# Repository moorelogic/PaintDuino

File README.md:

# PaintDuino

## Introduction
The PaintDuino is an Arduino Leonardo compatible, universal paintball marker control board.

### Features:
* Easily programmed with Arduino IDE
* Interface for 128 x 32 OLED display
* Two high current solenoid drivers
* RGB LED for status and trigger programming
* Supports both switched and push button On/Off
* USB Mini B programming connector
* Near zero battery drain when powered off

## License
This work is licensed under a Creative Commons Attribution-ShareAlike 3.0 Unported License.

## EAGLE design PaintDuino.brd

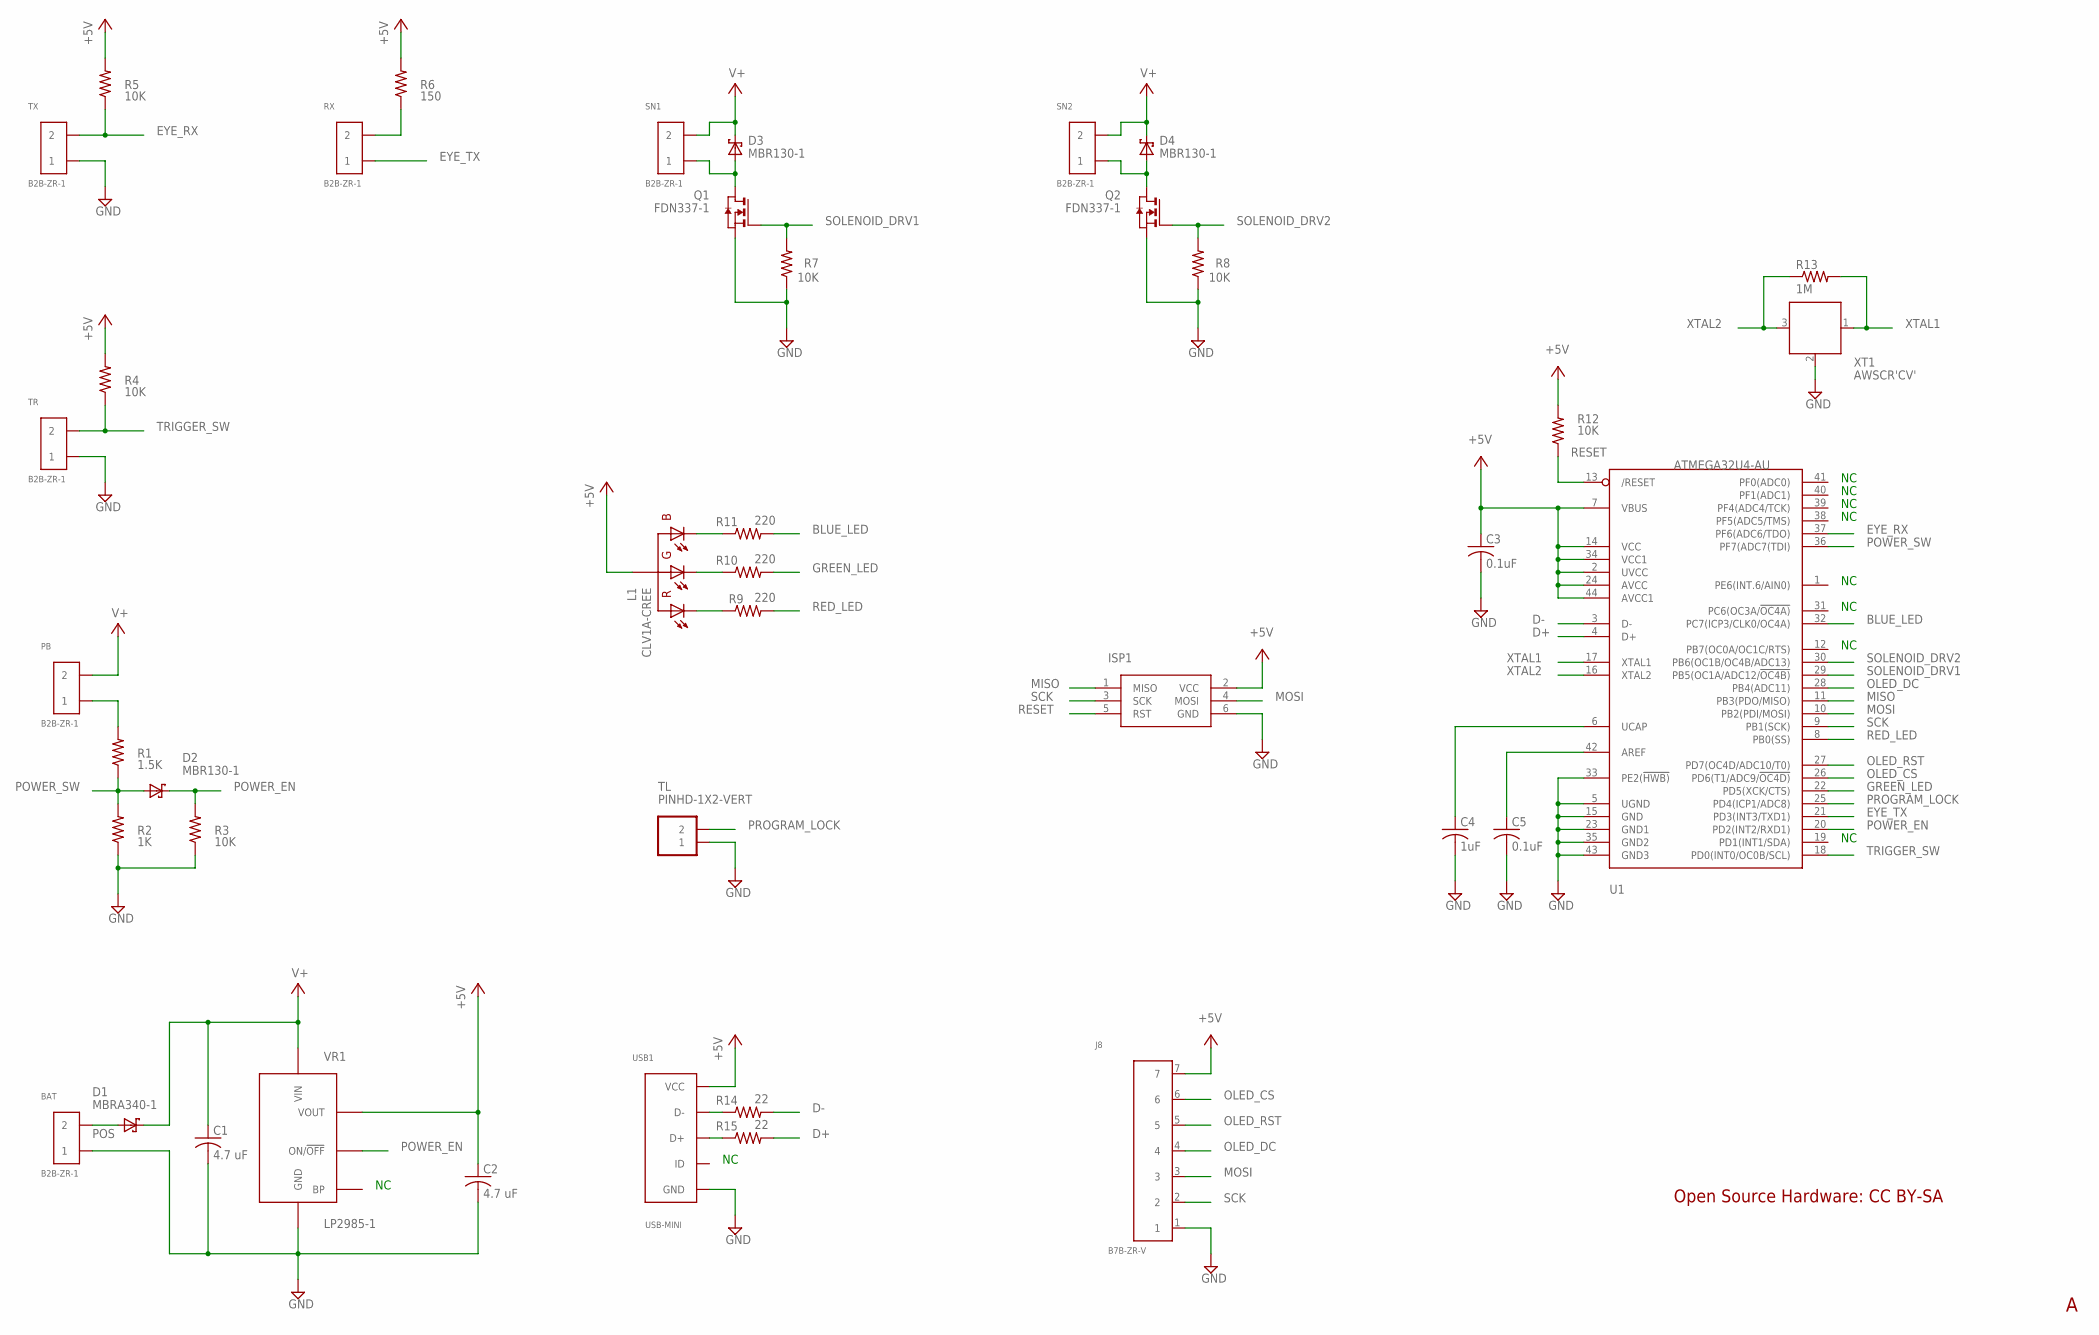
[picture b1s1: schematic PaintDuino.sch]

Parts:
BAT: B2B-ZR-1; B2B-ZR
C1, C2: 4.7 uF; C0805
C3, C5: 0.1uF; C0805
C4: 1uF; C0805
D1: MBRA340-1; DO214AC
D2, D3, D4: MBR130-1; SOD123
ISP1: AVRISP-6; AVRISP
J8: B7B-ZR-V; B7B-ZR
L1: CLV1A-CREE; PLCC4
PB: B2B-ZR-1; B2B-ZR
Q1, Q2: FDN337-1; SOT23
R1: 1.5K; R0805
R2: 1K; R0805
R3, R4, R5, R7, R8, R12: 10K; R0805
R6: 150; R0805
R9, R10, R11: 220; R0805
R13: 1M; R0805
R14, R15: 22; R0805
RX: B2B-ZR-1; B2B-ZR
SN1, SN2: B2B-ZR-1; B2B-ZR
TL: PINHD-1X2-VERT; 1X02
TR: B2B-ZR-1; B2B-ZR
TX: B2B-ZR-1; B2B-ZR
U1: ATMEGA32U4-AU; TQFP44
USB1: USB-MINI; USB-M2
VR1: LP2985-1; SOT23-5
XT1: AWSCR'CV'; AWSCR-CV

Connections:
+5V: C2.1, C3.1, ISP1.2 (VCC), J8.7, L1.2-CA (A), R4.2, R5.2, R6.2, R12.2, U1.2 (UVCC), U1.7 (VBUS), U1.14 (VCC), U1.24 (AVCC), U1.34 (VCC1), U1.44 (AVCC1), USB1.1 (VCC), VR1.5 (VOUT)
AREF: C5.1, U1.42 (AREF)
BC: L1.3-B (BC), R11.1
BLUE_LED: R11.2, U1.32 (PC7(ICP3/CLK0/OC4A))
D+: R15.2, U1.4 (D+)
D-: R14.2, U1.3 (D-)
EYE_C: R6.1, RX.2
EYE_RX: R5.1, TX.2, U1.37 (PF6(ADC6/TDO))
EYE_TX: RX.1, U1.21 (PD3(INT3/TXD1))
GC: L1.4-G (GC), R10.1
GND: BAT.1, C1.2, C2.2, C3.2, C4.2, C5.2, ISP1.6 (GND), J8.1, Q1.2 (S), Q2.2 (S), R2.1, R3.1, R7.1, R8.1, TL.1, TR.1, TX.1, U1.5 (UGND), U1.15 (GND), U1.23 (GND1), U1.33 (PE2(!HWB)), U1.35 (GND2), U1.43 (GND3), USB1.5 (GND), VR1.2 (GND), XT1.2
GREEN_LED: R10.2, U1.22 (PD5(XCK/CTS))
MISO: ISP1.1 (MISO), U1.11 (PB3(PDO/MISO))
MOSI: ISP1.4 (MOSI), J8.3, U1.10 (PB2(PDI/MOSI))
unnamed: R14.1, USB1.2 (D-)
unnamed: R15.1, USB1.3 (D+)
OLED_CS: J8.6, U1.26 (PD6(T1/ADC9/!OC4D))
OLED_DC: J8.4, U1.28 (PB4(ADC11))
OLED_RST: J8.5, U1.27 (PD7(OC4D/ADC10/T0))
PB: PB.1, R1.2
POS: BAT.2, D1.A
POWER_EN: D2.C, R3.2, U1.20 (PD2(INT2/RXD1)), VR1.3 (ON/!OFF)
POWER_SW: D2.A, R1.1, R2.2, U1.36 (PF7(ADC7(TDI))
PROGRAM_LOCK: TL.2, U1.25 (PD4(ICP1/ADC8))
Q1_D: D3.A, Q1.3 (D), SN1.1
Q2_D: D4.A, Q2.3 (D), SN2.1
RC: L1.1-R (RC), R9.1
RED_LED: R9.2, U1.8 (PB0(SS))
RESET: ISP1.5 (RST), R12.1, U1.13 (/RESET)
SCK: ISP1.3 (SCK), J8.2, U1.9 (PB1(SCK))
SOLENOID_DRV1: Q1.1 (G), R7.2, U1.29 (PB5(OC1A/ADC12/!OC4B))
SOLENOID_DRV2: Q2.1 (G), R8.2, U1.30 (PB6(OC1B/OC4B/ADC13))
TRIGGER_SW: R4.1, TR.2, U1.18 (PD0(INT0/OC0B/SCL))
UCAP: C4.1, U1.6 (UCAP)
V+: C1.1, D1.C, D3.C, D4.C, PB.2, SN1.2, SN2.2, VR1.1 (VIN)
XTAL1: R13.2, U1.17 (XTAL1), XT1.1
XTAL2: R13.1, U1.16 (XTAL2), XT1.3

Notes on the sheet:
Open Source Hardware: CC BY-SA

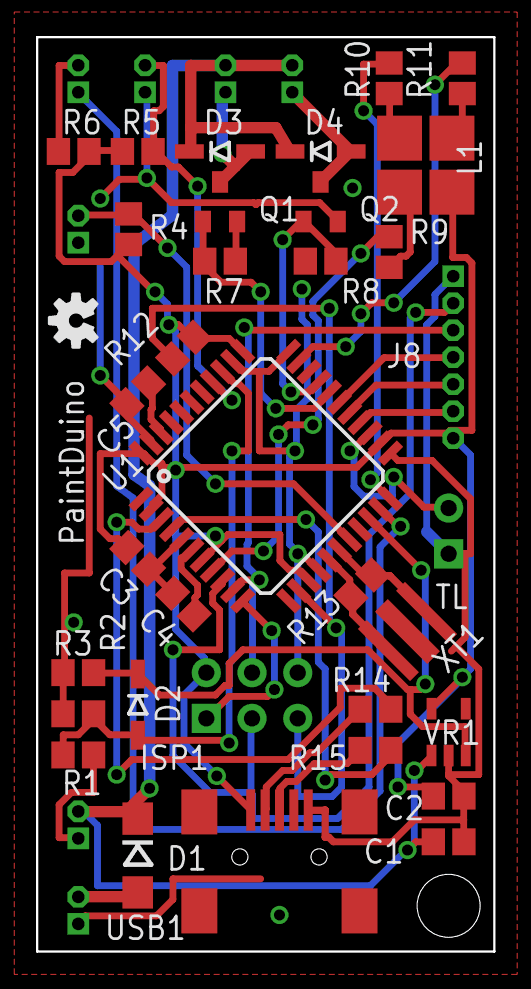
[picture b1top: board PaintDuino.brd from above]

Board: 2 copper layers, 25.4 x 50.8 mm, 42 parts (0 on the bottom side), 37 nets.

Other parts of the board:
U$1: OSHW-LOGO-S

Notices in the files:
parts and their libraries:
SparkFun-Aesthetics: Licensing: CC v3.0 Share-Alike You are welcome to use this library for commercial purposes.
